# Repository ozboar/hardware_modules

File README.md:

# Hardware Modules
A repository for custom open-source hardware modules, for various keyboards.

* [One Key module without LED](/modules/without-led/README.md)
* [Zoom65 V3 ScreenKey MX module](/modules/Zoom65v3/screenkey-mx/README.md) (work in progress)

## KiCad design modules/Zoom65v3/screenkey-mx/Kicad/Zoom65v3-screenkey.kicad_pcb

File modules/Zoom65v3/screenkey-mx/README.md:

## ScreenKey MX Module v0.1 (untested)

Replacement module for the Zoom65 V3 one-key position. It keeps the `onekey-no-led` outline, holes, switch position and ribbon pin order, and adds a Waveshare 0.85in ScreenKey keycap on a soldered MX switch. The keyboard's MCU drives the display over the 14-pin ribbon.

**v0.1 prototype ordered, not yet built or tested.** The MX fit below has only been checked in CAD.

All images and PDFs are plain KiCad exports. The switch model is simplified, the keycap geometry comes from Waveshare's STEP file, the connector models come from LCSC's EasyEDA library, and the ribbon's bow is an estimate. The blue screen area is a placeholder. The front silkscreen carries a simplified logo about 5 mm wide in the bottom-left corner.

### Parts

| Ref | Part | Purpose |
|---|---|---|
| Keycap | Waveshare 0.85in ScreenKey LCD B, SKU 34087 | Display, plugs into J1, not on the BOM |
| SW1 | MX-style switch | Soldered into plated holes with no plate, rotated 180 degrees so its pins sit south of the center post |
| Optional | Press-in pin sockets for MX switch pins | Not on the BOM, for later hot-swap use |
| J1 | Hirose FH34SRJ-12S-0.5SH(50), LCSC C424659 | 12-pin flex connector, top and bottom contact |
| J2 | Hirose FH34SRJ-14S-0.5SH(50), LCSC C324724 | 14-pin ribbon connector, top and bottom contact |
| U1 | PAM2804AAB010, LCSC C71463 | Backlight driver, in TSOT-25 |
| L1 | Murata DFE201612P-2R2M=P2, LCSC C79317 | 2.2 uH backlight inductor |
| R1 | UNI-ROYAL 0603WAF510KT5E, LCSC C25197 | 5.1R current sense, sets about 20 mA. The panel drawing says 20 mA and its table says 30-60 mA. Waveshare's board uses 5.6R, about 18 mA |
| C2, C3 | 10 uF, LCSC C19702 | Backlight driver output and input |
| R2 | 100k | Holds the backlight off until firmware drives it |
| R3, R4 | 10k | Hold RST and CS inactive |
| C1 | 100 nF | Panel supply decoupling |

The backlight is dimmed with PWM on the driver's EN pin. Its datasheet recommends 500 Hz.

### Ribbon Cable (J2)

| Pin | MCU | Net | Meter check at the MCU |
|---:|---:|---|---|
| 2 | - | `GND` | Continuity to ground |
| 4 | C6 | `KEY_ROW` (row 0) | Through a main board diode, 0.564 V from C6 to pin 4 |
| 5 | B1 | `KEY_COL` (column 14) | Continuity |
| 6 | A8 | `LCD_BL_PWM` | Continuity |
| 7 | B13 | `LCD_DC` | Continuity |
| 8 | C11 | `LCD_SCK` | Continuity |
| 9 | C10 | `LCD_MOSI` | Continuity |
| 10 | - | `+3V3` | 3.3 V with the keyboard powered |
| 12 | C14 | `LCD_RST` | Continuity |
| 13 | C13 | `LCD_CS` | Continuity |
| 14 | - | `GND` | Continuity to ground |

These checks were made on one keyboard and prove connections only. No key press or display signal has been tested through the ribbon. To find pin 1, look for ground on the 2nd contact in from one end: that end holds pin 1, and C13 is 2nd in from the other end.

The keyboard's main board already has the key's diode, so the module needs none. The main board schematic disagrees with these measurements at pin 2, which it leaves blank, and pin 4.

Pins 1, 3 and 11 are not connected. Pin 3 reads like pin 4 from ground, about 1.09 V in diode mode, but its source was not traced. Pins 1 and 11 were not measured. Switch pin 1 carries `KEY_ROW` and pin 2 carries `KEY_COL`. Firmware must disable the encoder and UART3, and use an ST7735 driver. The switch is rotated 180 degrees, but the keycap stays right side up: the ribbon and thin bezel are at the top, and the wide bezel is at the bottom. The key stays in the normal matrix.

### Keycap Connector (J1)

| Pin | Panel | Net |
|---:|---|---|
| 1, 12 | GND | `GND` |
| 2 | LEDK | `LED_K` |
| 3, 4 | NC | Not connected |
| 5 | LEDA | `LED_A` |
| 6 | VDD | `+3V3` |
| 7 | DC | `LCD_DC` |
| 8 | CS | `LCD_CS` |
| 9 | SCLK | `LCD_SCK` |
| 10 | MOSI | `LCD_MOSI` |
| 11 | RST | `LCD_RST` |

### Assembly

1. Solder the switch to the board and trim its side pins and contact pins close to the back. The center post stays intact. The keyboard plate is cut out here, so only the board holds the switch.
2. Pass the flex through the board's top-edge notch.
3. Plug the flex into J1, then press the keycap onto the stem.
4. Plug the ribbon into J2.

### Risks to check before ordering

- **Keycap tail fit:** the panel drawing shows a 0.30 +/-0.05 mm tail with 0.35 +/-0.04 mm fingers. J1 recommends 0.30 +/-0.03 mm and 0.30 +/-0.03 mm, so a tail at the tolerance limit could be loose or tight. Test J1 with a real keycap.

- **Stem fit:** the keycap's socket is 2.9 mm deep with 1.16 mm arms in Waveshare's CAD. A typical MX stem is about 3.6 mm tall with arms of about 1.17 and 1.31 mm, from memory rather than a drawing, so the wider arm may be tight.
- **Flex slack:** J1 is now about 6 mm closer to the notch, leaving about 7 mm of extra flex. This depends on the MX height, which is from memory.
- **Center post:** it stays intact and sticks out about 1.7 mm behind the board, a figure from memory. J1's rear edge clears the post hole by about 0.3-1.2 mm, depending on which way the connector's full 3.8 mm depth extends. Check this against a real connector. Removing a soldered switch means desoldering it, and the keycap must come off first.
- **Rear clearance:** the extra flex forms a bow about 5.6 mm behind the board in the model and grows on each press. J1 and J2 stand 1 mm. The clearance in the case has not been measured, and this is now the main fit risk.
- **Keycap clearance:** the keycap is 21.89 x 25.13 mm and its top is about 20.8 mm above the board's front face. The case opening has not been checked.
- **Mounting:** the board keeps the 2.0 mm `onekey-no-led` holes, but what they fasten to has not been confirmed, so the renders show no posts or screws.
- **Ribbon fit:** the FH34 needs a 0.3 +/-0.03 mm ribbon end with about 1.5 mm of exposed contacts, and the ribbon has not been measured. Its dual contacts accept the ribbon either way up, so keep the pin order matched to the footprint. The pin map above was checked with a meter on the keyboard.

### Hot-swap Option

The 3.05 mm holes for a Kailh socket cannot also hold a soldered switch, so this board uses 1.7 mm plated holes. Hot-swap would need press-in pin sockets that fit those holes, or a board revision with the `onekey-no-led` socket footprint. The pin socket fit has not been checked.

### Files

- `Kicad/`: KiCad project. The schematic is in KiCad 9 format and the board was saved by KiCad 10, so open it in KiCad 10. The J1 footprint and U1 symbol are stored in the design, not in a library.
- `Kicad/production/`: Gerbers and drills, BOM and placement files for the back-side parts. SW1 is left out because it is hand-soldered. J1 and J2 placement uses the center of their pads, so check their position and rotation in the fab's preview, along with every other back-side part.
- `docs/schematic.pdf`, `docs/pcb-layout.pdf`: KiCad exports of the schematic and of each board side, with copper, silkscreen, pads and part labels.
- `Kicad/3d/`: 3D models used by the board. The small parts are from KiCad's library, and the connectors are from LCSC's EasyEDA library, so check their terms before redistributing them.
- `docs/module-assembly.step`: assembly model, including geometry from Waveshare's STEP file.
- `docs/ScreenKey-Module-drawing.pdf`: Waveshare's module drawing.

DRC reports no violations and no unconnected items. The one parity warning is a `Datasheet` field difference on SW1. The routes were planned by hand and written by a script, and the board has not been opened in the KiCad GUI.

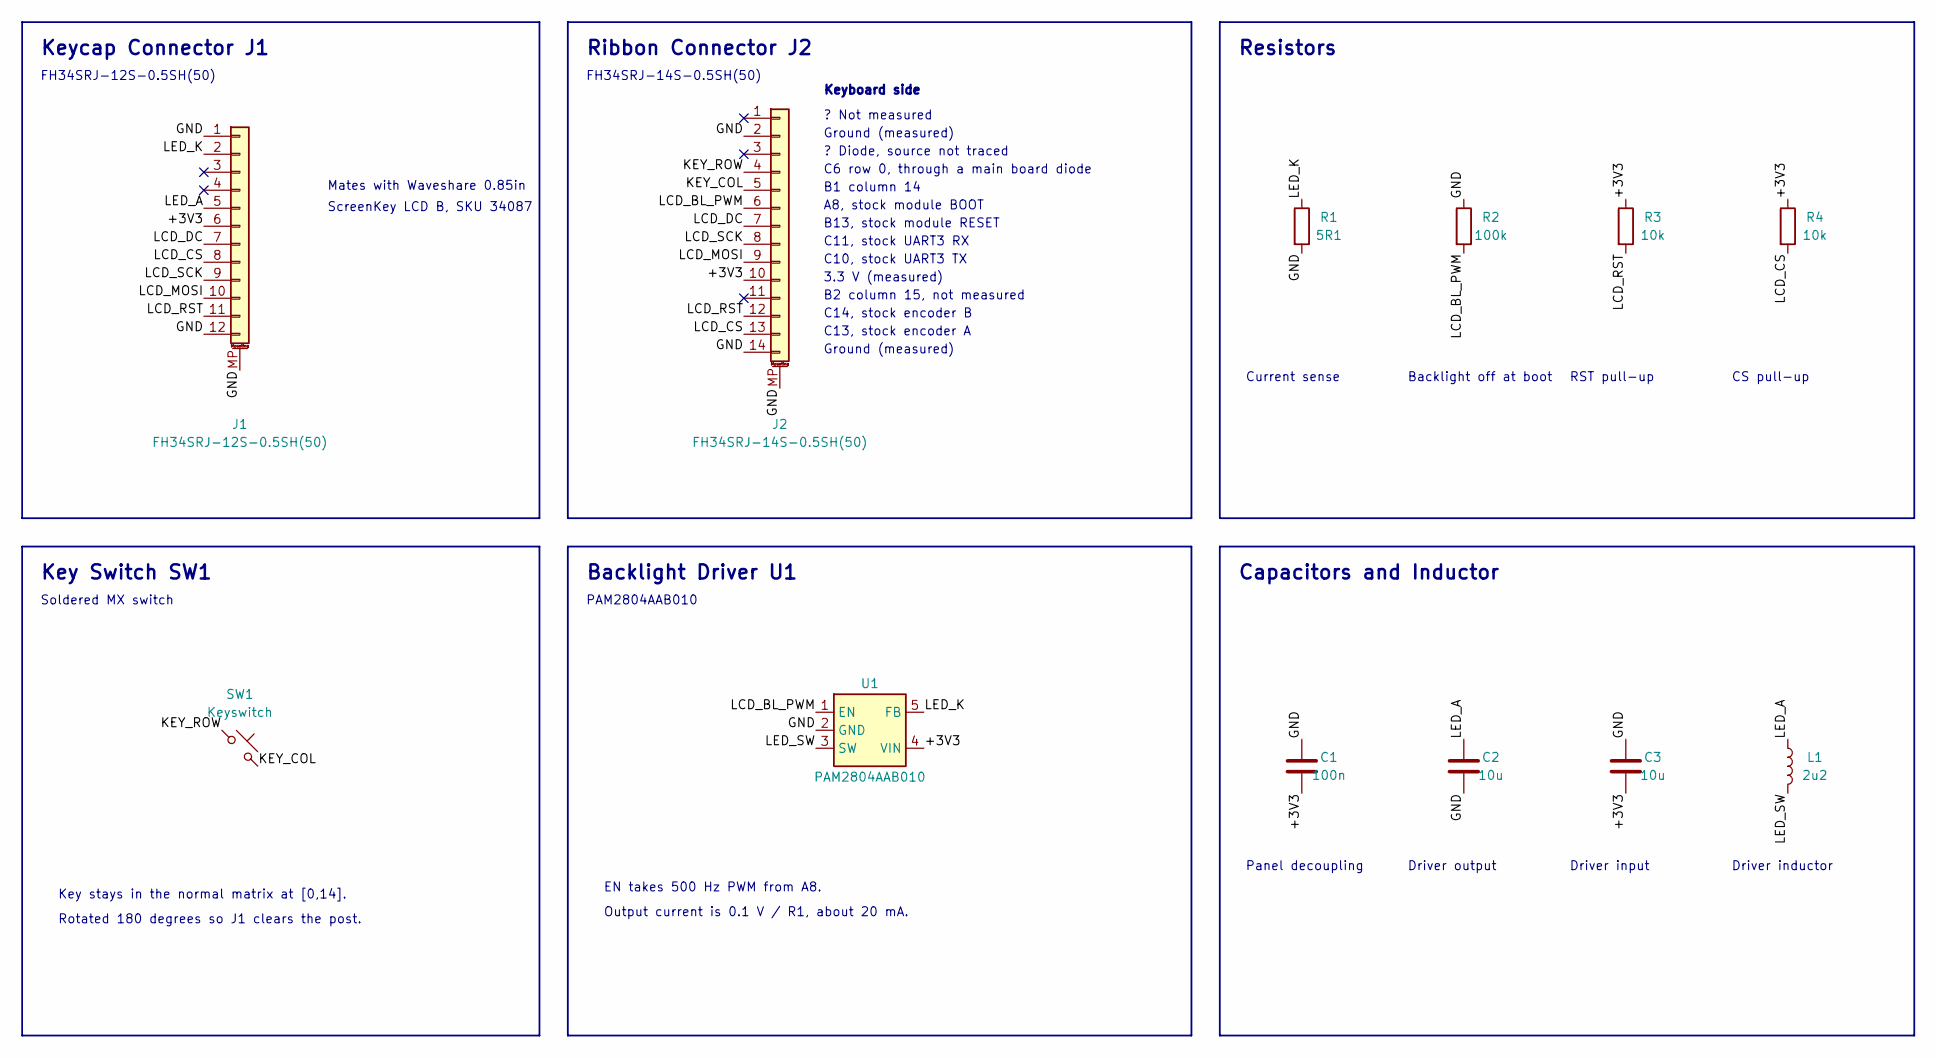
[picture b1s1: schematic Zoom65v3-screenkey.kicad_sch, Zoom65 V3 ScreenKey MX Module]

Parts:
C1: 100n; C_0603_1608Metric; MPN CC0603KRX7R9BB104; LCSC C14663
C2, C3: 10u; C_0603_1608Metric; MPN CL10A106KP8NNNC; LCSC C19702
J1: FH34SRJ-12S-0.5SH(50); Hirose_FH34SRJ-12S-0.5SH; MPN FH34SRJ-12S-0.5SH(50); LCSC C424659
J2: FH34SRJ-14S-0.5SH(50); Hirose_FH34SRJ-14S-0.5SH; MPN FH34SRJ-14S-0.5SH(50); LCSC C324724
L1: 2u2; L_Murata_DFE201610P; MPN DFE201612P-2R2M=P2; LCSC C79317
R1: 5R1; R_0603_1608Metric; MPN 0603WAF510KT5E; LCSC C25197
R2: 100k; R_0603_1608Metric; MPN 0603WAF1003T5E; LCSC C25803
R3, R4: 10k; R_0603_1608Metric; MPN 0603WAF1002T5E; LCSC C25804
SW1: Keyswitch; SW_MX_PTH
U1: PAM2804AAB010; SOT-23-5; MPN PAM2804AAB010; LCSC C71463

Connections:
/+3V3: C1.2, C3.2, J1.6, J2.10, R3.1, R4.1, U1.4
/GND: C1.1, C2.2, C3.1, J1.1, J1.12, J1.MP, J2.2, J2.14, J2.MP, R1.2, R2.1, U1.2
/KEY_COL: J2.5, SW1.2
/KEY_ROW: J2.4, SW1.1
/LCD_BL_PWM: J2.6, R2.2, U1.1
/LCD_CS: J1.8, J2.13, R4.2
/LCD_DC: J1.7, J2.7
/LCD_MOSI: J1.10, J2.9
/LCD_RST: J1.11, J2.12, R3.2
/LCD_SCK: J1.9, J2.8
/LED_A: C2.1, J1.5, L1.1
/LED_K: J1.2, R1.1, U1.5
/LED_SW: L1.2, U1.3

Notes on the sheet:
Keycap Connector J1
FH34SRJ-12S-0.5SH(50)
Ribbon Connector J2
FH34SRJ-14S-0.5SH(50)
Resistors
Key Switch SW1
Soldered MX switch
Backlight Driver U1
PAM2804AAB010
Capacitors and Inductor
Mates with Waveshare 0.85in
ScreenKey LCD B, SKU 34087
Keyboard side
? Not measured
Ground (measured)
? Diode, source not traced
C6 row 0, through a main board diode
B1 column 14
A8, stock module BOOT
B13, stock module RESET
C11, stock UART3 RX
C10, stock UART3 TX
3.3 V (measured)
B2 column 15, not measured
C14, stock encoder B
C13, stock encoder A
Key stays in the normal matrix at [0,14].
Rotated 180 degrees so J1 clears the post.
EN takes 500 Hz PWM from A8.
Output current is 0.1 V / R1, about 20 mA.
Current sense
Backlight off at boot
RST pull-up
CS pull-up
Panel decoupling
Driver output
Driver input
Driver inductor

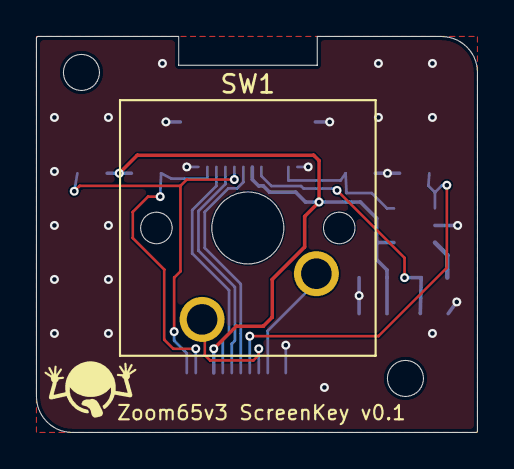
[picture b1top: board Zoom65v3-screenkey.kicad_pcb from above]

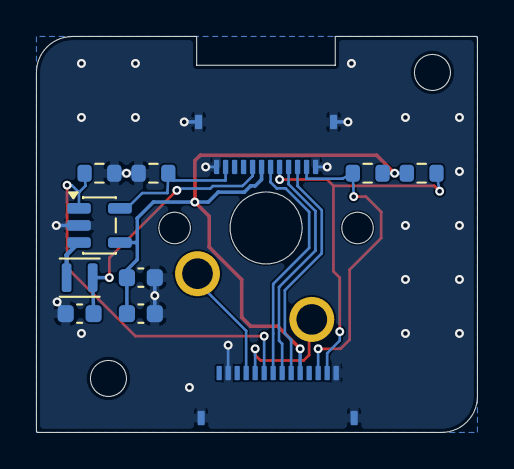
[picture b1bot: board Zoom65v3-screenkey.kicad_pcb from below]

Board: 2 copper layers, 24.5 x 22.0 mm, 12 parts (11 on the bottom side), 13 nets.

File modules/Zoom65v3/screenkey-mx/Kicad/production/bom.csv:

Comment,Designator,Footprint,Quantity,MPN,LCSC Part #
100n,C1,C_0603_1608Metric,1,CC0603KRX7R9BB104,C14663
10u,"C2,C3",C_0603_1608Metric,2,CL10A106KP8NNNC,C19702
FH34SRJ-12S-0.5SH(50),J1,Hirose_FH34SRJ-12S-0.5SH,1,FH34SRJ-12S-0.5SH(50),C424659
FH34SRJ-14S-0.5SH(50),J2,Hirose_FH34SRJ-14S-0.5SH,1,FH34SRJ-14S-0.5SH(50),C324724
2u2,L1,L_Murata_DFE201610P,1,DFE201612P-2R2M=P2,C79317
5R1,R1,R_0603_1608Metric,1,0603WAF510KT5E,C25197
100k,R2,R_0603_1608Metric,1,0603WAF1003T5E,C25803
10k,"R3,R4",R_0603_1608Metric,2,0603WAF1002T5E,C25804
PAM2804AAB010,U1,SOT-23-5,1,PAM2804AAB010,C71463

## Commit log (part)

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2025-08-20 v0.1 one-key-without-led
2025-08-21 chore: rename module folder to include board name (zoom65v3)
2025-09-14 docs: change img paths on readme
2026-01-10 add and apply .gitignore
